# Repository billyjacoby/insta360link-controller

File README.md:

# Link Control for macOS

A native macOS controller for Insta360 Link cameras, with live preview, menu-bar
controls, and Raycast integration. The desktop app includes its USB camera helper
and runtime libraries; users do not need Homebrew or the official Insta360 app.

This fork builds on [jfwoods/insta360link-controller](https://github.com/jfwoods/insta360link-controller).
The original CLI, ESP32 joystick firmware, and KiCad hardware designs remain included.
This is an independent, unofficial project, not an Insta360 product.

**Status: experimental preview.** See the [release guide](docs/releasing.md),
[known limitations](host/linkctl-gui/README.md), and [licensing status](NOTICE.md).
Builds are currently ad-hoc signed, not notarized. Each packaged build reports its
actual architecture and minimum macOS version; these depend on the bundled libraries.

## Native macOS app

A SwiftUI desktop client is available in [`host/linkctl-gui`](host/linkctl-gui)
with local video preview, automatic service management, camera movement, and
device-discovered image settings (white balance, focus, color, and more where supported),
plus Link 2 Pro tracking, DeskView, overhead, and whiteboard camera modes.
The packaged app includes its camera service and runtime libraries. It starts the
service and detects the model automatically—users do not choose an executable or
install Homebrew. Open the app, select your camera, and start preview.
It also provides a persistent menu-bar menu and bundled
[Raycast Script Commands](integrations/raycast/README.md) for camera controls,
preview, image settings, and AI modes, all using the app's existing connection.
### Included controls

| Feature | Desktop app |
| --- | --- |
| Live camera preview | Explicit start/stop; stays fixed above scrolling settings |
| Movement | Bounded pan/tilt jogs, adjustable speed, center, manual stop |
| Zoom | 100–400% |
| Image settings | Device-discovered color, focus, and white balance controls |
| Link 2 Pro modes | Normal, tracking, DeskView, overhead, automatic whiteboard |
| Link 2 Pro gestures | Master enable/disable and individual palm, L, and V gesture switches |
| Menu bar | Common controls, preview, status, and dashboard reopening |
| Raycast | 13 bundled Script Commands; no separate daemon required |

Available image controls depend on the camera. Tracking speed/framing, gesture
bindings, proprietary exposure/ISO, and HDR are not implemented. Gesture switches
use the official SDK protocol with USB readback; physical behavior and power-cycle
persistence still need verification on the connected camera.
See the [documentation index](docs/README.md) for usage, protocols, and release steps.

**Model compatibility:** the GUI automatically detects the original Link
(`2e1a:4c01`) or Link 2 Pro (`2e1a:4c06`) and checks advertised controls before use.
The standalone daemon defaults to the original Link; use `--auto-camera` or
`--link2-pro` for the Pro. Live preview, zoom write/readback, and a
short pan/stop have been verified with video active on connected hardware. Start
preview first: this camera acknowledged writes without applying them in standby.
Tilt and center still need physical verification.
See [hardware findings](host/linkctl-probe/FINDINGS.md). Preview availability does
not imply that motor/vendor controls are compatible.

## Architecture

```text
Raycast / menu bar / SwiftUI dashboard
                  │
                  ▼
        App-owned bundled helper ──USB/UVC──> Insta360 Link camera
        (private loopback WebSocket)

Advanced / joystick setup (separate from desktop app):
ESP32 ──WebSocket──> standalone daemon ──USB/UVC──> camera
CLI   ──TCP───────> standalone daemon
```
The GUI does not depend on a manually installed daemon or the legacy TCP port.
Do not run both control services against the same camera.

## Future work

- Saved image profiles and camera position presets
- Additional verified Link 2 Pro controls
- Developer ID signing and notarization
- Broader hardware and platform validation

## Setup

### Desktop app (recommended)

### Install a packaged build

When a GUI build is available from this fork's
[releases](https://github.com/billyjacoby/insta360link-controller/releases) or
[successful CI artifacts](https://github.com/billyjacoby/insta360link-controller/actions/workflows/ci.yml):

1. Choose the package matching your Mac's architecture and check its minimum OS.
2. Unzip it and move **Link Control.app** to `/Applications`.
3. Open the app and wait for **Camera ready**.
4. Click **Start Preview** and allow camera access, then use the controls.

Keep a video stream active for Link 2 Pro controls. Closing the dashboard leaves
the app in the menu bar; choose **Quit Link Control** to stop its helper.
Current packages are ad-hoc signed, not notarized.

### Build and install locally

With Xcode command-line tools and Homebrew installed, run from the repository root:

```sh
brew install cmake libwebsockets cjson openssl@3 pkgconf
bash host/linkctl-gui/scripts/package-app.sh
bash host/linkctl-gui/scripts/install-local.sh
open '/Applications/Link Control.app'
```

Quit an existing instance before installation. The installer preserves an existing
app as a backup. Homebrew is needed only at build time.

### Connect Raycast

From the app's menu-bar menu, choose **Open Raycast Scripts Folder**. Add that
folder in **Raycast Settings → Extensions → + → Add Script Directory**; the app
copies its path for the folder picker. See the [Raycast guide](integrations/raycast/README.md)
for commands and hotkey setup.

See [full app instructions](host/linkctl-gui/README.md) and the
[local validation and release checklist](docs/releasing.md).

The standalone daemon/CLI instructions below are for advanced use and ESP32 setups.

## Standalone daemon, CLI, and joystick setup

### 1. Install the Mac daemon

The daemon controls the Insta360 Link over USB and exposes a WebSocket + TCP interface for clients.

**Option A: Download the latest release**

When available, download `linkctl-daemon-*-macos-*.tar.gz` from this fork's [releases](https://github.com/billyjacoby/insta360link-controller/releases), then:

```bash
tar xzf linkctl-daemon-*-macos-*.tar.gz
cd linkctl-daemon
./install.sh
```

**Option B: Build from source**

```bash
# Install dependencies
brew install libwebsockets cjson openssl@3 pkgconf

# Build
cd host/linkctl-daemon
mkdir -p build && cd build
PKG_CONFIG_PATH="/opt/homebrew/lib/pkgconfig:$PKG_CONFIG_PATH" cmake ..
make

# Run
./linkctl-daemon
```

The daemon finds the Insta360 Link over USB, starts a WebSocket server on port 9000 and a TCP control socket on port 9001, and advertises itself via mDNS.

### 2. Install the CLI client (optional)

**Option A: Download the latest release**

When available, download `linkctl-*-macos-*.tar.gz` from this fork's [releases](https://github.com/billyjacoby/insta360link-controller/releases), then:

```bash
tar xzf linkctl-*-macos-*.tar.gz
sudo cp linkctl/linkctl /usr/local/bin/
```

**Option B: Build from source**

```bash
cd host/linkctl
mkdir -p build && cd build
cmake ..
make

# Optional: install system-wide
sudo cmake --install . --prefix /usr/local
```

Or run directly from the build directory: `./build/linkctl <command>`.

### 3. Flash ESP32 firmware (if using joystick controller)

Requires [PlatformIO](https://platformio.org/).

```bash
pio run --target upload
```

### 4. Configure WiFi on the ESP32 (if using joystick controller)

On first boot, the ESP32 starts a captive portal:

1. Connect to the **Insta360-Controller** WiFi network from your phone or laptop
2. A setup page opens automatically — enter your WiFi network name and password
3. The ESP32 saves the credentials and reboots onto your network

Alternatively, configure via the serial CLI (115200 baud):

```
wifi MyNetwork MyPassword
connect
```

### 5. Use it

**CLI:** Run `linkctl status` to verify the daemon is running and the camera is connected, then use `linkctl jog` for interactive control.

**Joystick:** Move the joystick to pan and tilt the camera. The ESP32 reads the analog input, converts it to direction and speed, and sends commands to the daemon over WebSocket. The ESP32 discovers the daemon automatically via mDNS — no IP configuration needed.

## Dependencies

### Daemon (`linkctl-daemon`)

| Dependency | Source | Purpose |
|-----------|--------|---------|
| [libwebsockets](https://libwebsockets.org/) | Homebrew | WebSocket server |
| [cJSON](https://github.com/DaveGamble/cJSON) | Homebrew | JSON parsing |
| [OpenSSL 3](https://www.openssl.org/) | Homebrew | Required by libwebsockets |
| IOKit | macOS (built-in) | USB device access |
| CoreFoundation | macOS (built-in) | System data structures |
| dns_sd | macOS (built-in) | mDNS advertisement |

### CLI (`linkctl`)

No external dependencies — pure POSIX C.

### ESP32 Firmware

| Dependency | Source | Purpose |
|-----------|--------|---------|
| [arduinoWebSockets](https://github.com/Links2004/arduinoWebSockets) | PlatformIO (`links2004/WebSockets@^2.4.1`) | WebSocket client |
| [ArduinoJson](https://github.com/bblanchon/ArduinoJson) | PlatformIO (`bblanchon/ArduinoJson@^7.0.0`) | JSON encoding/parsing |
| [PlatformIO](https://platformio.org/) | CLI or VS Code extension | Build toolchain (Arduino framework) |

## Daemon Options

```
./linkctl-daemon                  # Default: port 9000, mDNS enabled
./linkctl-daemon --port 8080      # Custom port
./linkctl-daemon --no-mdns        # Disable mDNS advertisement
./linkctl-daemon --test           # Test camera control and exit
./linkctl-daemon --status         # Read camera status and exit, without writes
./linkctl-daemon --link2-pro --status  # Read-only check of experimental Link 2 Pro profile
./linkctl-daemon --link2-pro      # Run with experimental Link 2 Pro controls
./linkctl-daemon --auto-camera   # Automatically detect Link or Link 2 Pro
./linkctl-daemon --auto-camera --loopback --no-control --no-mdns --port 19000
                                # Private desktop-app service (normally automatic)
```

## CLI Client (`linkctl`)

`linkctl` is a lightweight command-line client for controlling the Insta360 Link via the daemon's TCP control socket. It has zero external dependencies (pure POSIX C) and connects to the daemon at `localhost:9001`.

### Commands

| Command | Description |
|---------|-------------|
| `linkctl help` | Show usage information |
| `linkctl status` | Show camera connection state and current zoom |
| `linkctl center` | Center the gimbal and reset zoom to 1.0x |
| `linkctl zoom <1.0-4.0>` | Set zoom level (e.g., `linkctl zoom 2.5`) |
| `linkctl zoom` | Show the current zoom level |
| `linkctl stop` | Stop all gimbal movement |
| `linkctl jog` | Enter interactive pan/tilt mode |

### Jog Mode

`linkctl jog` enters an interactive mode for real-time camera control using keyboard input.

| Key | Action |
|-----|--------|
| `W` | Tilt up |
| `S` | Tilt down |
| `A` | Pan left |
| `D` | Pan right |
| `+` / `=` | Increase speed |
| `-` | Decrease speed |
| Space | Stop movement |
| `C` | Center gimbal |
| `Q` / ESC | Exit jog mode |

Movement continues while a key is held (via terminal key repeat) and automatically stops ~400ms after release. Default speeds: pan=15, tilt=10. Speed range: 3-30 (pan), 3-20 (tilt).

## ESP32 Serial CLI

Connect to the ESP32's serial port at 115200 baud. Type `help` for a full list.

| Command | Description |
|---------|-------------|
| `wifi <ssid> [pass]` | Set WiFi credentials |
| `connect` | Connect to WiFi and daemon |
| `disconnect` | Disconnect |
| `status` | Show connection state |
| `stop` | Stop gimbal movement |
| `center` | Center the gimbal |
| `joy` | Test joystick output (5 sec) |
| `calibrate` | Calibrate joystick center point |
| `invertx` / `inverty` | Toggle axis inversion |
| `portal` | Start captive portal for WiFi setup |
| `webconfig` | Start web config on current network |
| `host <ip>` | Override daemon IP (skip mDNS) |
| `port <port>` | Override daemon port |
| `clear` | Clear all saved config |
| `reboot` | Restart ESP32 |

## Protocol

The daemon exposes two interfaces:

- **WebSocket** on port **9000** — for the ESP32 joystick controller (JSON over WebSocket text frames)
- The native GUI uses the same WebSocket API with the **`arduino`** subprotocol.
- **TCP** on port **9001** — for the `linkctl` CLI client (newline-terminated text commands)

### WebSocket Commands (ESP32 → Daemon)

```json
{"cmd": "pan_tilt", "pan_dir": 1, "pan_speed": 15, "tilt_dir": 255, "tilt_speed": 10}
{"cmd": "zoom", "value": 250}
{"cmd": "stop"}
{"cmd": "center"}
{"cmd": "status"}
```

### WebSocket Responses (Daemon → ESP32)

```json
{"type": "status", "camera_connected": true, "zoom": 150}
{"type": "ack"}
{"type": "error", "message": "camera not found"}
```

Direction encoding: `1` = positive (right/up), `255` = negative (left/down), `0` = stop. Speed ranges: pan 0-30, tilt 0-20, zoom 100-400.

The GUI also reads and edits supported camera image settings using `settings_get`
and `setting_set`. Both return a device-reported `settings` snapshot; errors use
`settings_error` so a rejected setting does not disconnect movement controls.
See [camera settings and wire schema](docs/camera-settings.md).
The Link 2 Pro mode interface and remaining AI feature gaps are documented in
[AI camera controls](docs/ai-camera-controls.md).

## How It Works

The Insta360 Link exposes pan/tilt/zoom controls as UVC extension unit registers accessible over USB. The `linkctl-daemon` writes to these registers directly using macOS IOKit, bypassing the Insta360 desktop app entirely. The daemon runs a WebSocket server on port 9000 that accepts JSON commands and translates them into the appropriate UVC control transfers, plus a TCP control socket on port 9001 for the `linkctl` CLI. The ESP32 reads the joystick, discovers the daemon via mDNS, and streams movement commands over WiFi. For use without an ESP32, the `linkctl` CLI connects to the daemon's TCP socket and sends commands directly from the terminal.

## Testing

Status-only transport regression tests for the GUI (no camera required). The tests
send no movement commands; the daemon performs its normal stop during shutdown.
Stop any existing daemon first so TCP port 9001 is available:

```bash
python3 -m venv host/linkctl-daemon/build/test-env
host/linkctl-daemon/build/test-env/bin/pip install websocket-client
host/linkctl-daemon/build/test-env/bin/python host/linkctl-daemon/test_gui_transport.py -v
```

The daemon includes an integration test suite that exercises WebSocket communication, camera control, error handling, and multi-client support. Requires the Insta360 Link to be connected.

```bash
# Run all tests (camera will move)
python3 host/linkctl-daemon/test_daemon.py

# Skip tests that move the camera
python3 host/linkctl-daemon/test_daemon.py --skip-motion
```

## Hardware

### ESP32-WROOM-32 (Breadboard Prototype)

| Function | GPIO | Notes |
|----------|------|-------|
| Joystick X (pan) | 34 | ADC1, input only |
| Joystick Y (tilt) | 35 | ADC1, input only |
| Joystick button (home) | 32 | ADC1, internal pull-up, active low |
| Zoom potentiometer | 33 | ADC1 |
| I2C SDA | 21 | Hardware I2C default |
| I2C SCL | 22 | Hardware I2C default |
| Calibrate button | 25 | Internal pull-up, active low |
| Spare button | 26 | Internal pull-up, active low |
| Status LED | 2 | On-board LED |

> **Note:** Use ADC1 pins (GPIO 32-39) for analog inputs — ADC2 conflicts with WiFi on the ESP32. GPIO 0/1/3/6-11/12/15 are reserved (boot/flash/UART/strapping).

**LED status patterns:**
- **Solid** — Connected to daemon, camera ready
- **Fast blink** — Connected to daemon, waiting for camera
- **Slow blink** — WiFi connecting
- **Off** — No connection

### ESP32-S3-WROOM (PCB)

| Function | GPIO | Notes |
|----------|------|-------|
| Joystick X (pan) | 4 | ADC1 |
| Joystick Y (tilt) | 5 | ADC1 |
| Joystick button (home) | 13 | Internal pull-up, active low |
| Zoom potentiometer | 6 | ADC1 |
| I2C SDA (OLED + fuel gauge) | 8 | S3 default I2C SDA |
| I2C SCL (OLED + fuel gauge) | 9 | S3 default I2C SCL |
| Calibrate button | 14 | Internal pull-up, active low |
| Spare button | 15 | Internal pull-up, active low |
| Status LED (connectivity) | 16 | External LED |
| Status LED (TBD) | 17 | External LED |
| Status LED (TBD) | 18 | External LED |
| USB D- | 19 | Native USB (reserved) |
| USB D+ | 20 | Native USB (reserved) |

> **Note:** Use ADC1 pins (GPIO 1-10) for analog inputs — ADC2 conflicts with WiFi on the S3. GPIO 19/20 are reserved for native USB.

## Project Structure

```
├── platformio.ini                   # ESP32 build config
├── src/
│   ├── main.cpp                     # Setup and main loop
│   ├── config.h                     # Pin definitions, constants
│   ├── joystick.h/cpp               # Analog input, deadzone, calibration
│   ├── wifi_manager.h/cpp           # WiFi connection handling
│   ├── websocket_client.h/cpp       # WebSocket + mDNS discovery
│   ├── commands.h/cpp               # JSON command encoding
│   ├── serial_cli.h/cpp             # Serial CLI
│   ├── status_led.h/cpp             # LED status patterns
│   ├── zoom.h/cpp                   # Zoom potentiometer input
│   └── captive_portal.h/cpp         # AP mode WiFi config portal
├── host/
│   ├── linkctl/
│   │   ├── CMakeLists.txt           # CLI build config
│   │   ├── linkctl.c                # CLI client implementation
│   │   └── README.md                # CLI usage documentation
│   └── linkctl-daemon/
│       ├── CMakeLists.txt           # Daemon build config
│       ├── main.c                   # Entry point and event loop
│       ├── camera.c/h               # IOKit USB camera control
│       ├── server.c/h               # WebSocket server
│       ├── control.c/h              # TCP control socket (for CLI)
│       ├── mdns.c/h                 # mDNS advertisement
│       ├── install.sh               # Installation script
│       ├── service.sh               # launchd service management
│       └── test_daemon.py           # Integration test suite
└── hardware/
    ├── insta360-joystick.kicad_pro  # KiCad project
    ├── insta360-joystick.kicad_sch  # Schematic
    ├── insta360-joystick.kicad_pcb  # PCB layout
    ├── specs.md                     # Hardware specs and pin assignments
    ├── Components/                  # KiCad symbols and footprints
    └── Datasheets/                  # Component datasheets
```

-----

**GenAI Disclaimer:** I'm a hardware guy-- I *tolerate* writing code, but I don't love it. So while the hardware design is truly my own work product, Claude Code has been used to support firmware/software development. All code is still reviewed by me before release.

**Commit Message Disclaimer:** I apologize if my commit messages are occasionally less than informative-- this is a weekend project for me, and sometimes I'm a silly goose.

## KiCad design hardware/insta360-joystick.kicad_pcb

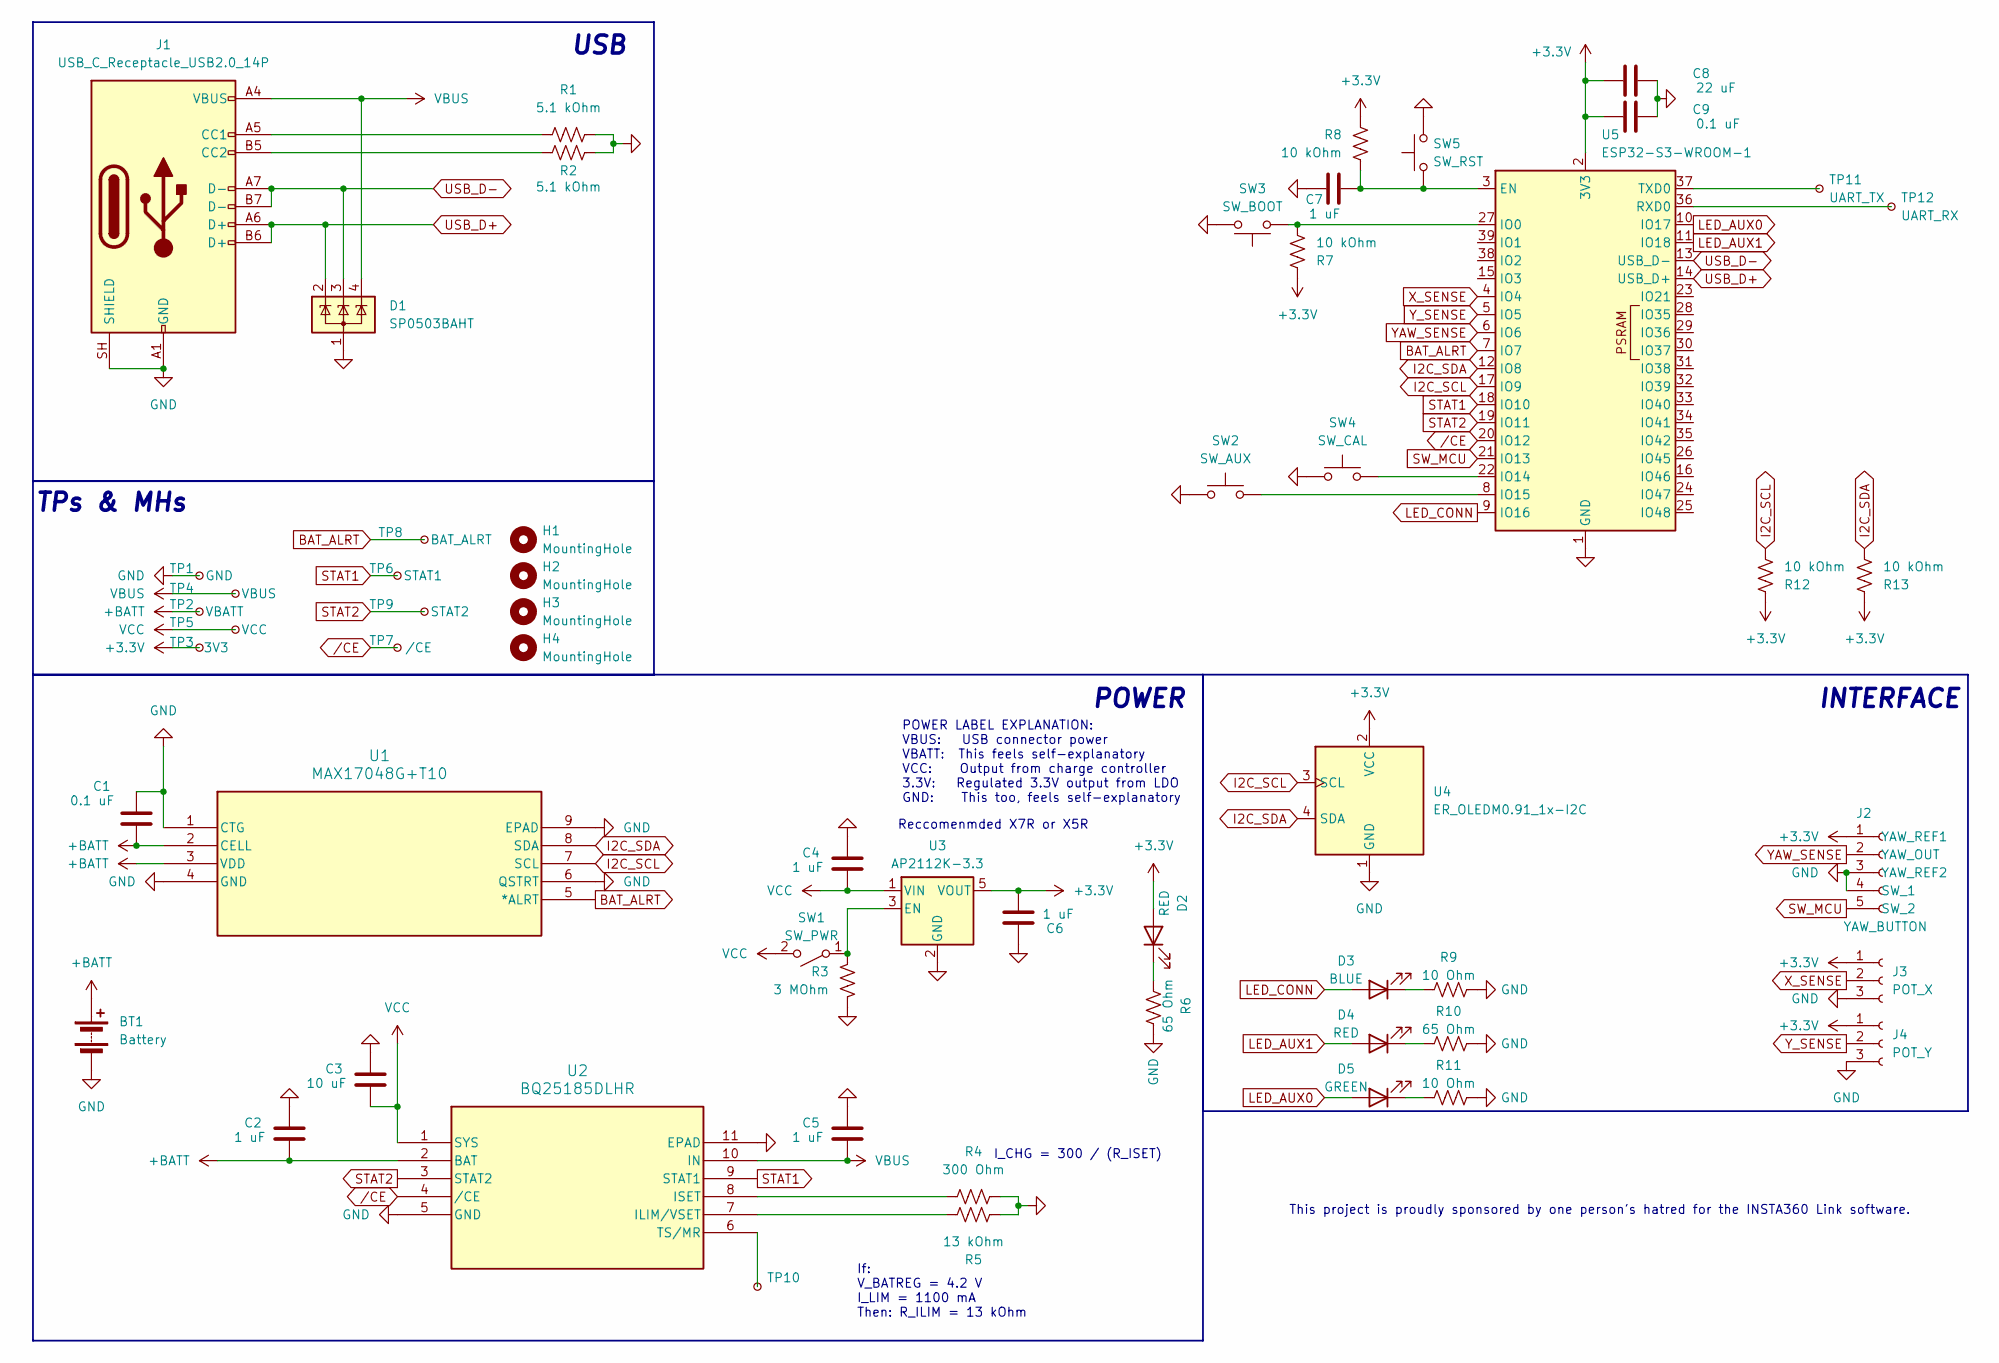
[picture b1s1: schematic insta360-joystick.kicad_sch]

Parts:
BT1: Battery; 18650_Holder
C1, C9: 0.1 uF; C_0603_1608Metric
C2, C4, C5, C6, C7: 1 uF; C_0603_1608Metric
C3: 10 uF; C_0603_1608Metric
C8: 22 uF; C_0603_1608Metric
D1: SP0503BAHT; SOT-143
D2, D4: RED; D_1206_3216Metric
D3: BLUE; D_1206_3216Metric
D5: GREEN; D_1206_3216Metric
H1, H2, H3, H4: MountingHole; MountingHole_2.2mm_M2_Pad_TopBottom
J1: USB_C_Receptacle_USB2.0_14P; USB_C_Receptacle_GCT_USB4105-xx-A_16P_TopMnt_Horizontal
J2: YAW_BUTTON; PinHeader_1x05_P1.27mm_Vertical
J3: POT_X; PinHeader_1x03_P2.54mm_Vertical
J4: POT_Y; PinHeader_1x03_P2.54mm_Vertical
R1, R2: 5.1 kOhm; R_0603_1608Metric
R3: 3 MOhm; R_0603_1608Metric
R4: 300 Ohm; R_0603_1608Metric
R5: 13 kOhm; R_0603_1608Metric
R6, R10: 65 Ohm; R_0603_1608Metric
R7, R8, R12, R13: 10 kOhm; R_0603_1608Metric
R9, R11: 10 Ohm; R_0603_1608Metric
SW1: SW_PWR; SW_L101011ML04Q
SW2: SW_AUX; ME02150F3502
SW3: SW_BOOT; SW_Push_SPST_NO_Alps_SKRK
SW4: SW_CAL; ME02150F3502
SW5: SW_RST; SW_Push_SPST_NO_Alps_SKRK
TP1: GND; TestPoint_THTPad_D2.0mm_Drill1.0mm
TP2: VBATT; TestPoint_THTPad_D2.0mm_Drill1.0mm
TP3: 3V3; TestPoint_THTPad_D2.0mm_Drill1.0mm
TP4: VBUS; TestPoint_THTPad_D2.0mm_Drill1.0mm
TP5: VCC; TestPoint_THTPad_D2.0mm_Drill1.0mm
TP6: STAT1; TestPoint_THTPad_D2.0mm_Drill1.0mm
TP7: /CE; TestPoint_THTPad_D2.0mm_Drill1.0mm
TP8: BAT_ALRT; TestPoint_THTPad_D2.0mm_Drill1.0mm
TP9: STAT2; TestPoint_THTPad_D2.0mm_Drill1.0mm
TP10: TestPoint_Small; TestPoint_Bridge_Pitch2.0mm_Drill0.7mm
TP11: UART_TX; TestPoint_THTPad_D2.0mm_Drill1.0mm
TP12: UART_RX; TestPoint_THTPad_D2.0mm_Drill1.0mm
U1: MAX17048G+T10; 21-0168E_T822-3_MXM
U2: BQ25185DLHR; WSON10_DLH_TEX
U3: AP2112K-3.3; SOT-23-5
U4: ER_OLEDM0.91_1x-I2C
U5: ESP32-S3-WROOM-1

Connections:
+3.3V: C6.2, C8.2, C9.2, D2.2 (A), J2.1 (YAW_REF1), J3.1, J4.1, R7.1, R8.1, R12.1, R13.1, TP3.1 (1_1), U3.5 (VOUT), U4.2 (VCC), U5.2 (3V3)
+BATT: BT1.1 (+), C1.2, C2.2, TP2.1 (1_1), U1.2 (CELL), U1.3 (VDD), U2.2 (BAT)
BAT_ALRT: TP8.1 (1_1), U1.5 (*ALRT), U5.7 (IO7)
GND: BT1.2 (-), C1.1, C2.1, C3.1, C4.1, C5.1, C6.1, C7.1, C8.1, C9.1, D1.1 (A), J1.A1 (GND), J1.A12 (GND), J1.B1 (GND), J1.B12 (GND), J1.SH (SHIELD), J2.3 (YAW_REF2), J2.4 (SW_1), J3.3, J4.3, R1.2, R2.2, R3.1, R4.2, R5.2, R6.2, R9.2, R10.2, R11.2, SW2.1, SW3.1, SW4.1, SW5.2, TP1.1 (1_1), U1.1 (CTG), U1.4 (GND), U1.6 (QSTRT), U1.9 (EPAD), U2.5 (GND), U2.11 (EPAD), U3.2 (GND), U4.1 (GND), U5.1 (GND), U5.40 (GND), U5.41 (GND)
I2C_SCL: R12.2, U1.7 (SCL), U4.3 (SCL), U5.17 (IO9)
I2C_SDA: R13.2, U1.8 (SDA), U4.4 (SDA), U5.12 (IO8)
LED_AUX0: D5.2 (A), U5.10 (IO17)
LED_AUX1: D4.2 (A), U5.11 (IO18)
LED_CONN: D3.2 (A), U5.9 (IO16)
unnamed: D2.1 (K), R6.1
unnamed: D3.1 (K), R9.1
unnamed: D4.1 (K), R10.1
unnamed: D5.1 (K), R11.1
unnamed: J1.A5 (CC1), R1.1
unnamed: J1.B5 (CC2), R2.1
unnamed: R3.2, SW1.1 (A), U3.3 (EN)
unnamed: R5.1, U2.7 (ILIM/VSET)
unnamed: R4.1, U2.8 (ISET)
unnamed: TP10.1 (1_1), U2.6 (TS/MR)
unnamed: C7.2, R8.2, SW5.1, U5.3 (EN)
unnamed: R7.2, SW3.2, U5.27 (IO0)
unnamed: SW4.2, U5.22 (IO14)
unnamed: SW2.2, U5.8 (IO15)
unnamed: TP12.1 (1_1), U5.36 (RXD0)
unnamed: TP11.1 (1_1), U5.37 (TXD0)
STAT1: TP6.1 (1_1), U2.9 (STAT1), U5.18 (IO10)
STAT2: TP9.1 (1_1), U2.3 (STAT2), U5.19 (IO11)
SW_MCU: J2.5 (SW_2), U5.21 (IO13)
USB_D+: D1.2 (K), J1.A6 (D+), J1.B6 (D+), U5.14 (USB_D+)
USB_D-: D1.3 (K), J1.A7 (D-), J1.B7 (D-), U5.13 (USB_D-)
VBUS: C5.2, D1.4 (K), J1.A4 (VBUS), J1.A9 (VBUS), J1.B4 (VBUS), J1.B9 (VBUS), TP4.1 (1_1), U2.10 (IN)
VCC: C3.2, C4.2, SW1.2 (B), TP5.1 (1_1), U2.1 (SYS), U3.1 (VIN)
X_SENSE: J3.2, U5.4 (IO4)
YAW_SENSE: J2.2 (YAW_OUT), U5.6 (IO6)
Y_SENSE: J4.2, U5.5 (IO5)
/CE: TP7.1 (1_1), U2.4 (/CE), U5.20 (IO12)

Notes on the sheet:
If: V_BATREG = 4.2 V I_LIM = 1100 mA Then: R_ILIM = 13 kOhm
POWER LABEL EXPLANATION: VBUS: USB connector power VBATT: This feels self-explanatory VCC: Output from charge controller 3.3V: Regulated 3.3V output from LDO GND: This too, feels self-explanatory
USB
TPs & MHs
POWER
I_CHG = 300 / (R_ISET)
Reccomenmded X7R or X5R
This project is proudly sponsored by one person's hatred for the INSTA360 Link software.
INTERFACE

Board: 2 copper layers, 58 parts (1 on the bottom side), 36 nets, no tracks yet.

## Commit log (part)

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2026-03-29 Write `README.md`
2026-03-31 Add ESP32-S3 build target, fix some joystick issues
2026-03-31 Initial schematic work and component sourcing
2026-03-31 Add wifi connection retries
2026-04-02 Initial zoom implementation plan for prototype validation
2026-04-02 Initial zoom implementation
2026-04-02 Switching to ADC absolute-based zoom control
2026-04-02 Cleaning up appendages of old implementations
2026-04-02 Moving `commands.cpp/.h` functionality into `websocket_client.cpp`
2026-04-03 Fixing a build config
2026-04-03 Making the robots do what I want
2026-04-03 Getting the right datasheets
2026-04-03 Ok I think the schematic is done?
2026-04-03 Update `README.md`
2026-04-03 Beginning PCB implementation
2026-04-03 Changing restart command name and adding zoom on/off commands
2026-04-03 Adding autocal to joystick at runtime
2026-04-04 Make stop command also center gimbal
2026-04-04 Rehoming the camera after calibration
2026-04-04 Still trying to fix random movement bug
2026-04-04 Making the robots do what I want (part 432423560)
2026-04-04 Making a CI-CD pipeline
2026-04-04 Update `.gitignore` and clean up directories
2026-04-04 Update `.gitignore` the sequel
2026-04-04 Adding hardware component files
2026-04-04 Making a cli client controller for macOS
2026-04-04 Adding snazzy badges!
2026-04-04 Revise `README.md`
2026-04-04 CLI Implementation!!! And some daemon changes to add new access interface.
2026-04-04 Fixing some of the robot's suggestions
2026-04-04 Updating CI-CD pipeline to build CLI client as well
2026-04-04 Update `README.md` (part one bajillion)
2026-04-04 Making the robots do what I want type of commit
